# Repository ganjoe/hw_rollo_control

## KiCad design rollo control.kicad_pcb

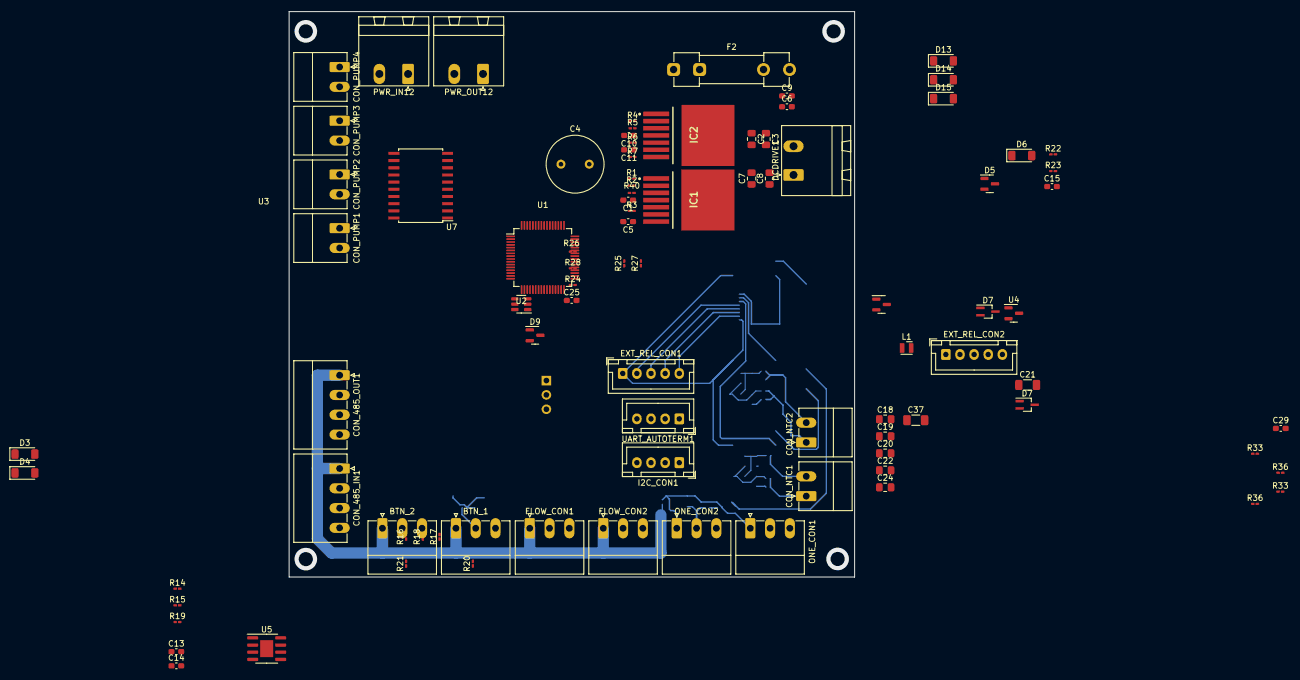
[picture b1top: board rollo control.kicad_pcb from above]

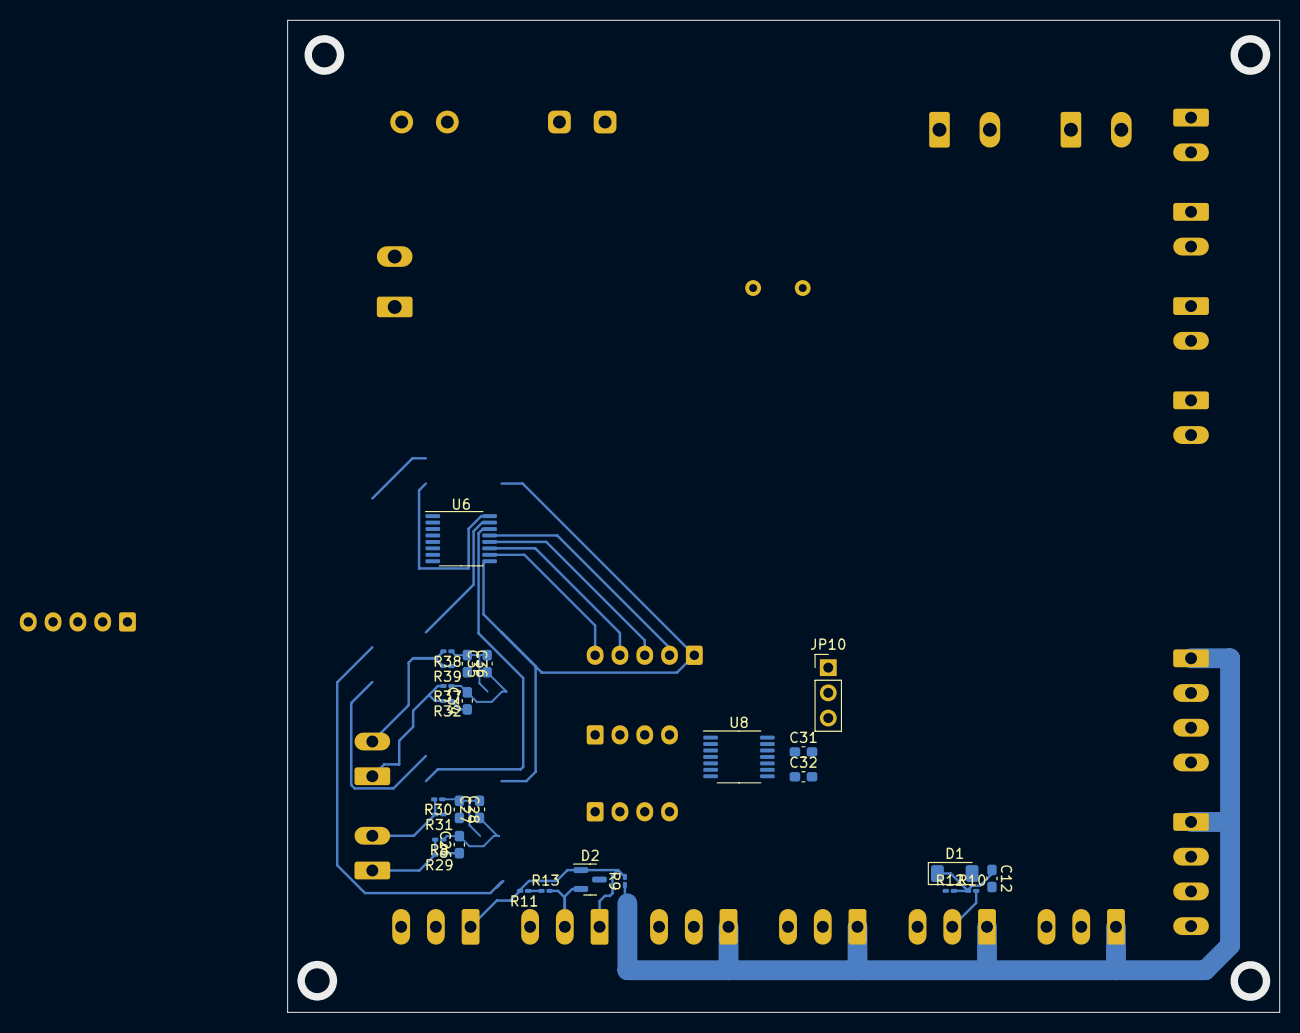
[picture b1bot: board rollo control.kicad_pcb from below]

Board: 4 copper layers, 100.0 x 100.0 mm, 118 parts (27 on the bottom side), 59 nets.

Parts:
BTN_1, BTN_2: Conn_01x03; PhoenixContact_MC_1,5_3-G-3.5_1x03_P3.50mm_Horizontal
C1, C5, C10, C11, C29, C31, C32: C_Small; C_0603_1608Metric_Pad1.08x0.95mm_HandSolder
C2, C3, C7, C8: 220nF; C_0805_2012Metric_Pad1.18x1.45mm_HandSolder
C4: 1000uF; C_Radial_D10.0mm_H16.0mm_P5.00mm
C6, C9, C25: 100nF; C_0603_1608Metric_Pad1.08x0.95mm_HandSolder
C12, C13: 100n; C_0603_1608Metric_Pad1.08x0.95mm_HandSolder
C14, C15: 10n; C_0603_1608Metric_Pad1.08x0.95mm_HandSolder
C18: 100nF; C_0805_2012Metric_Pad1.18x1.45mm_HandSolder
C19, C20: 22uF; C_0805_2012Metric_Pad1.18x1.45mm_HandSolder
C21, C37: 10uF; C_1206_3216Metric_Pad1.33x1.80mm_HandSolder
C22: 10uF; C_0805_2012Metric_Pad1.18x1.45mm_HandSolder
C24: C_Small; C_0805_2012Metric_Pad1.18x1.45mm_HandSolder
C26, C27, C28, C34, C35, C36: 1u; C_0603_1608Metric_Pad1.08x0.95mm_HandSolder
CON_485_IN1, CON_485_OUT1: Conn_01x04; PhoenixContact_MC_1,5_4-G-3.5_1x04_P3.50mm_Horizontal
CON_NTC1, CON_NTC2: Conn_01x02; PhoenixContact_MC_1,5_2-G-3.5_1x02_P3.50mm_Horizontal
CON_PUMP1, CON_PUMP2, CON_PUMP3, CON_PUMP4: Conn_01x02; PhoenixContact_MC_1,5_2-G-3.5_1x02_P3.50mm_Horizontal
D1, D3, D4, D6: BZV55C3V6; D_MiniMELF
D2, D5, D9: SP0502BAHT; SOT-23
D7, D7#2: BAV70S; SOT-323_SC-70_Handsoldering
D13, D14: BZV55B5V6; D_MiniMELF
D15: BZV55B3V6; D_MiniMELF
DCDRIVE1: Conn_01x02; PhoenixContact_MSTBA_2,5_2-G-5,08_1x02_P5.08mm_Horizontal
EXT_REL_CON1, EXT_REL_CON2: Conn_01x06; JST_XH_B5B-XH-A_1x05_P2.50mm_Vertical
F2: Fuse; Fuseholder_Clip-5x20mm_Littelfuse_100_Inline_P20.50x4.60mm_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
FLOW_CON1, FLOW_CON2: Conn_01x03; PhoenixContact_MC_1,5_3-G-3.5_1x03_P3.50mm_Horizontal
I2C_CON1: Conn_01x04; JST_XH_B4B-XH-A_1x04_P2.50mm_Vertical
IC1, IC2: IFX007TAUMA1; PG-TO263-7-1
JP10: Jumper_3_Bridged12; PinHeader_1x03_P2.54mm_Vertical
L1: 4u7; L_Wurth_WE-LQSH-2010
ONE_CON1, ONE_CON2: Conn_01x03; PhoenixContact_MC_1,5_3-G-3.5_1x03_P3.50mm_Horizontal
PWR_IN12: Conn_01x02; PhoenixContact_MSTBA_2,5_2-G-5,08_1x02_P5.08mm_Horizontal
PWR_OUT12: Conn_01x02; PhoenixContact_MSTBA_2,5_2-G-5,08_1x02_P5.08mm_Horizontal
R1, R2, R3, R4, R5, R6, R7, R40: R; R_0201_0603Metric_Pad0.64x0.40mm_HandSolder
R8, R10, R14, R17, R18, R19, R22, R29, R30, R31, R32, R37, R38, R39: 10k; R_0201_0603Metric_Pad0.64x0.40mm_HandSolder
R9, R20: 10meg; R_0201_0603Metric_Pad0.64x0.40mm_HandSolder
R11, R16: 0R; R_0201_0603Metric_Pad0.64x0.40mm_HandSolder
R12, R15, R21, R23: 22k; R_0201_0603Metric_Pad0.64x0.40mm_HandSolder
R13: 4K7; R_0201_0603Metric_Pad0.64x0.40mm_HandSolder
R24, R28: 1440; R_0201_0603Metric_Pad0.64x0.40mm_HandSolder
R25, R27: 20R; R_0201_0603Metric_Pad0.64x0.40mm_HandSolder
R26: 120R; R_0201_0603Metric_Pad0.64x0.40mm_HandSolder
R33, R33#2, R36, R36#2: R_0201_0603Metric_Pad0.64x0.40mm_HandSolder
U1: STM32G071RBTx; LQFP-64_10x10mm_P0.5mm
U2: AP63205WU; TSOT-23-6
U3: AP7384-33SA; SOT-23
U4: AP7384-50SA; SOT-23
U5: MAX485E; SOIC-8-1EP_3.9x4.9mm_P1.27mm_EP2.29x3mm
U6: ULN2004A; TSSOP-16_4.4x5mm_P0.65mm
U7: BTS724G; Infineon_PG-DSO-20-32
U8: TXB0104PW; TSSOP-14_4.4x5mm_P0.65mm
UART_AUTOTERM1: Conn_01x04; JST_XH_B4B-XH-A_1x04_P2.50mm_Vertical

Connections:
/12V0: C2.1, C3.1, C4.1, C6.1, C9.1, C21.1, C37.1, F2.2, IC1.7 (VS), IC2.7 (VS), R33.2, R33#2.2, U2.2 (EN), U2.3 (IN), U4.1 (VI), U7.1 (VBB), U7.10 (VBB), U7.11 (VBB), U7.12 (VBB), U7.15 (VBB), U7.16 (VBB), U7.19 (VBB), U7.20 (VBB)
/Analog-IN/5V0: C24.1, C26.1, C34.1, D7.1 (A), D7#2.1 (A), D13.1 (K), R29.1, R32.1, U4.2 (VO)
/Autoterm/3V3: C22.1, C31.1, D15.1 (K), JP10.1 (A), R11.1, R13.1, R16.1, R17.1, R18.1, U3.2 (VO), U8.1 (VCCA)
/Autoterm/5V0: BTN_1.1, BTN_2.1, C19.1, C20.1, C25.1, CON_485_IN1.1, CON_485_OUT1.1, D14.1 (K), EXT_REL_CON1.1, EXT_REL_CON2.1, FLOW_CON1.1, FLOW_CON2.1, JP10.3 (B), L1.2, R9.1, R20.1, R24.2, U2.1 (FB), U3.1 (VI), U5.8 (VCC), U6.9 (COM)
/GND: BTN_1.3, BTN_2.3, C1.2, C4.2, C5.2, C6.2, C7.2, C8.2, C9.2, C10.2, C11.2, C12.2, C13.2, C14.2, C15.2, C19.2, C20.2, C21.2, C22.2, C24.2, C25.2, C28.2, C29.2, C31.2, C32.2, C36.2, C37.2, CON_485_IN1.4, CON_485_OUT1.4, CON_PUMP1.2, CON_PUMP2.2, CON_PUMP3.2, CON_PUMP4.2, D1.2 (A), D2.3 (A), D3.2 (A), D4.2 (A), D5.3 (A), D6.2 (A), D9.3 (A), D13.2 (A), D14.2 (A), D15.2 (A), FLOW_CON1.3, FLOW_CON2.3, I2C_CON1.2, IC1.1 (GND), IC2.1 (GND), ONE_CON1.3, ONE_CON2.3, PWR_IN12.1, PWR_OUT12.1, R6.1, R12.1, R15.1, R21.1, R23.1, R28.1, R31.1, R36.1, R36#2.1, R39.1, R40.1, U2.4 (GND), U3.3 (GND), U4.3 (GND), U5.5 (GND), U6.8 (GND), U7.2 (GND1/2), U7.6 (GND3/4), U8.7 (GND), UART_AUTOTERM1.2
Ain_12V_Sig: C29.1, R33.1, R33#2.1, R36.2, R36#2.2
Ain_ntc0+: C26.2, C27.1, R8.1
Ain_ntc0-: C27.2, C28.1, R30.1
Ain_ntc1+: C34.2, C35.1, R37.1
Ain_ntc1-: C35.2, C36.1, R38.1
BTN_1: C12.1, D1.1 (K), R10.1, R12.2
BTN_2: C13.1, D3.1 (K), R14.1, R15.2
FLW_Sig1: C14.1, D4.1 (K), R19.1, R21.2
FLW_Sig2: C15.1, D6.1 (K), R22.1, R23.2
I2C_SCL: D5.1 (K), I2C_CON1.3, R17.2
I2C_SDA: D5.2 (K), I2C_CON1.4, R18.2
unnamed: BTN_1.2, R10.2
unnamed: BTN_2.2, R14.2
unnamed: CON_485_IN1.2, CON_485_OUT1.2, D9.2 (K), R24.1, R25.2, R26.2
unnamed: CON_485_IN1.3, CON_485_OUT1.3, D9.1 (K), R26.1, R27.2, R28.2
unnamed: CON_NTC1.1, R8.2, R29.2
unnamed: CON_NTC1.2, R30.2, R31.2
unnamed: CON_NTC2.1, R32.2, R37.2
unnamed: CON_NTC2.2, R38.2, R39.2
unnamed: CON_PUMP1.1, U7.18 (OUT1)
unnamed: CON_PUMP2.1, U7.17 (OUT2)
unnamed: CON_PUMP3.1, U7.14 (OUT3)
unnamed: CON_PUMP4.1, U7.13 (OUT4)
unnamed: C3.2, C8.1, DCDRIVE1.1, IC1.4 (OUT_1), IC1.8 (OUT_2)
unnamed: C2.2, C7.1, DCDRIVE1.2, IC2.4 (OUT_1), IC2.8 (OUT_2)
unnamed: EXT_REL_CON1.2, U6.13 (O4)
unnamed: EXT_REL_CON1.3, U6.12 (O5)
unnamed: EXT_REL_CON1.4, U6.11 (O6)
unnamed: EXT_REL_CON1.5, U6.10 (O7)
unnamed: EXT_REL_CON2.3, U6.16 (O1)
unnamed: EXT_REL_CON2.4, U6.15 (O2)
unnamed: EXT_REL_CON2.5, U6.14 (O3)
unnamed: FLOW_CON1.2, R19.2
unnamed: FLOW_CON2.2, R22.2
unnamed: I2C_CON1.1, R16.2, R20.2
unnamed: IC1.2 (IN), R1.2
unnamed: IC1.3 (INH), R2.2
unnamed: C5.1, IC1.6 (IS), R3.2
unnamed: C1.1, IC1.5 (SR), R40.2
unnamed: IC2.2 (IN), R4.2
unnamed: IC2.3 (INH), R5.2
unnamed: C11.1, IC2.6 (IS), R7.2
unnamed: C10.1, IC2.5 (SR), R6.2
unnamed: C32.1, JP10.2 (C), U8.14 (VCCB), UART_AUTOTERM1.1
unnamed: D2.1 (K), ONE_CON1.1, ONE_CON2.1, R9.2, R11.2
unnamed: F2.1, PWR_IN12.2, PWR_OUT12.2
unnamed: C18.2, U2.6 (BST)
unnamed: C18.1, L1.1, U2.5 (SW)
unnamed: R27.1, U5.6 (A)
unnamed: R25.1, U5.7 (B)
unnamed: U8.13 (B1), UART_AUTOTERM1.3
unnamed: U8.12 (B2), UART_AUTOTERM1.4
ONE_SIG: D2.2 (K), ONE_CON1.2, ONE_CON2.2, R13.2
enable: U5.2 (~RE), U5.3 (DE)

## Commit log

2023-06-14 first
2023-06-14 fsdf
2023-06-14 asdf
2023-06-14 sadf
2023-06-15 place
2023-06-19 mc1.5
2023-07-02 placing
2023-07-03 placing2
2023-07-05 ende
2023-08-09 dgfg
2023-09-26 gsdfg
    dyfg
